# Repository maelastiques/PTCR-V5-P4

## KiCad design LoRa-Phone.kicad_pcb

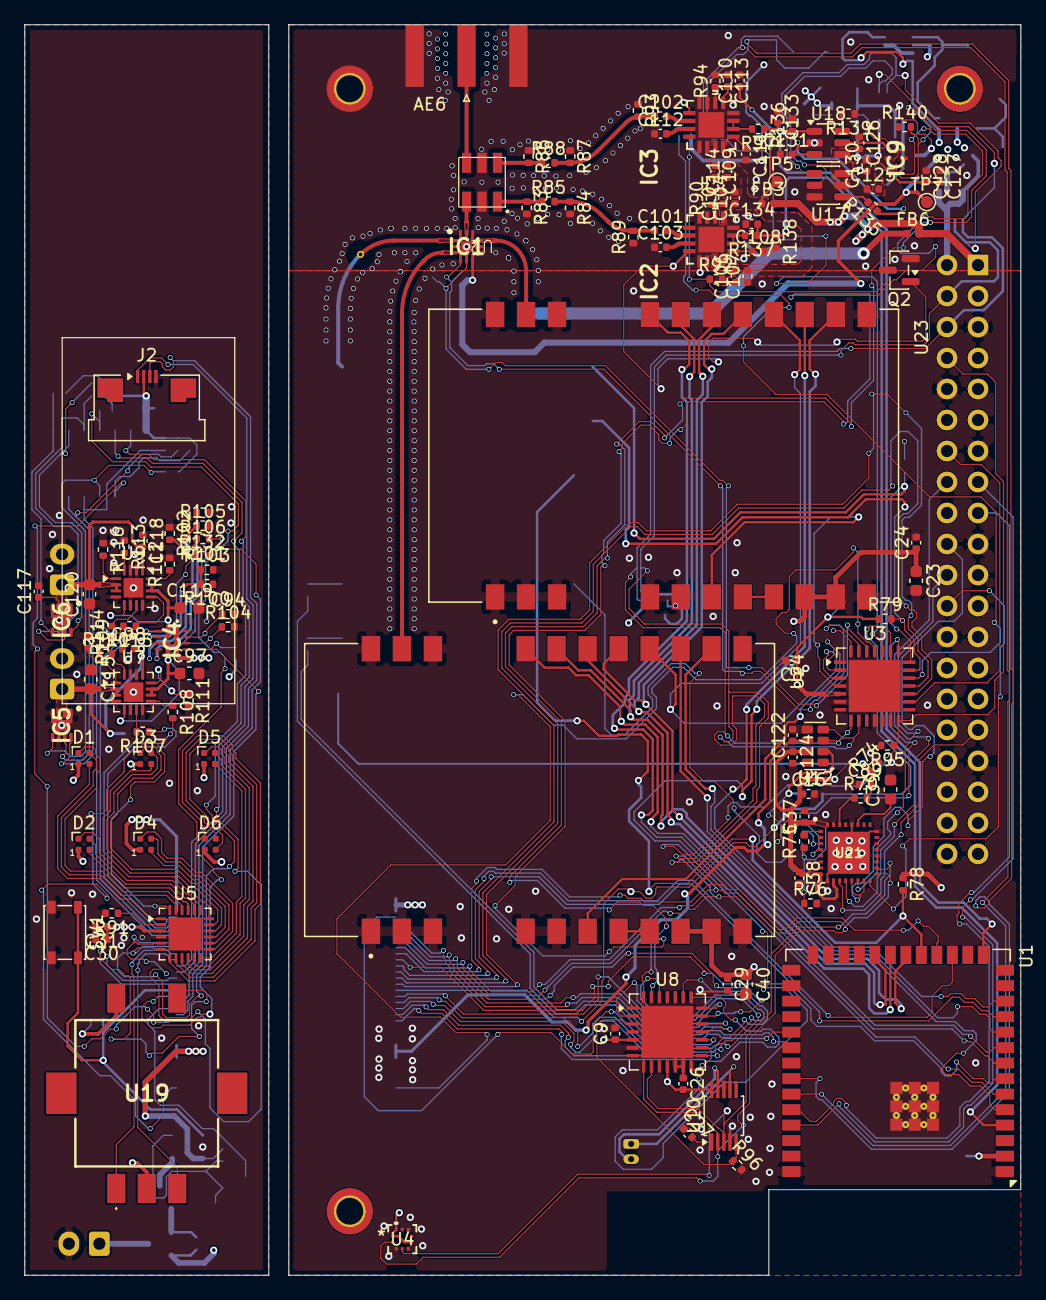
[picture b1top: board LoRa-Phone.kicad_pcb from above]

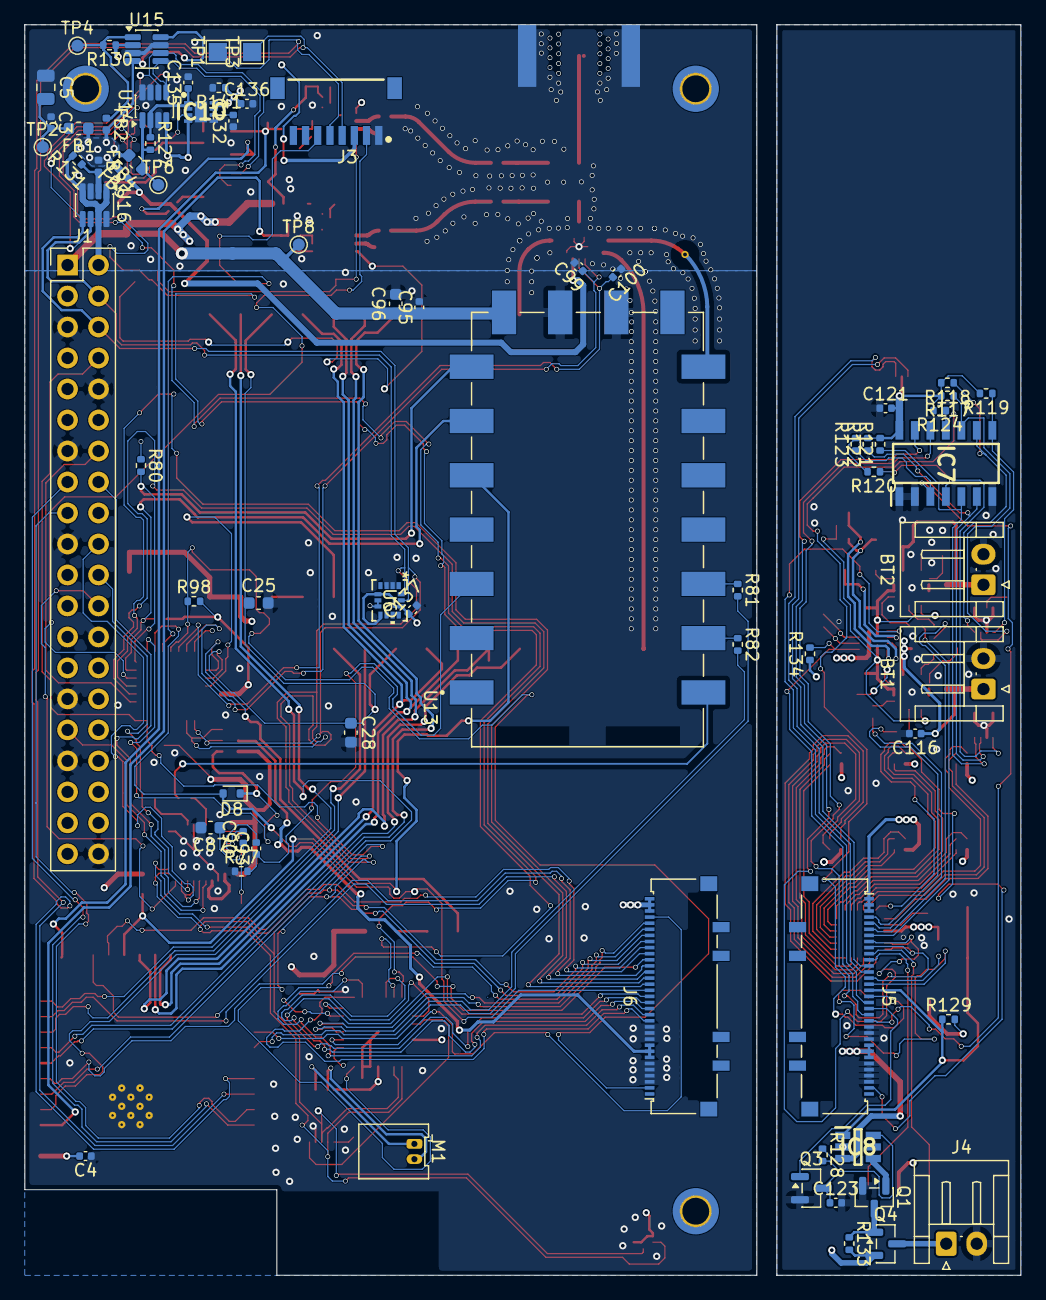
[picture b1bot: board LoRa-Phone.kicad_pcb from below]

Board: 4 copper layers, 81.6 x 102.5 mm, 203 parts (71 on the bottom side), 188 nets.

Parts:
AE6: SMA; SMA_Amphenol_132289_EdgeMount
BT1: MAIN; JST_EH_S2B-EH_1x02_P2.50mm_Horizontal
BT2: SECOND; JST_EH_S2B-EH_1x02_P2.50mm_Horizontal
C3, C4, C8, C9, C24, C29, C89, C90, C95, C121, C122, C123, C124, C125, C128, C130, C131, C132, C133, C134, C135, C137: 100nF; C_0402_1005Metric
C5: 47uF; C_0805_2012Metric
C16, C31, C37, C38, C94, C105, C107, C110, C114: 0.1uF; C_0402_1005Metric
C23, C25, C28, C40, C96: 10uF; C_0603_1608Metric
C26, C27, C30, C93, C98, C116, C117, C118: 1uF; C_0402_1005Metric
C39, C87, C97, C115, C119, C120: 4.7uF; C_0603_1608Metric
C99, C100, C104, C106, C109, C113: 100pF; C_0402_1005Metric
C101, C102, C103, C108, C111, C112: 1nF; C_0402_1005Metric
C126, C127: 2.2uF; C_0402_1005Metric
C136: 22uF; C_0402_1005Metric
D1, D2, D3, D4, D5, D6: LED_ARBG; LED_SK6812_EC15_1.5x1.5mm
D8: D; D_SOD-523
FB1: 600R @100MHz 2A; L_0603_1608Metric
FB2, FB3, FB5, FB6: 600R @100MHz 500mA; L_0402_1005Metric
FB4: 600R @100MHz 1.5A; L_0603_1608Metric
FB7: 600R @100MHz 4A; L_0402_1005Metric
IC1: SKY13373-460LF; QFN50P200X200X60-13N-D
IC2, IC3: AD8318ACPZ-REEL7; QFN65P400X400X100-17N
IC4: TPS2121RUXT
IC5, IC6: MAX17048G+T10; SON50P200X200X80-9N-D
IC7: TCA9543ADR; SOIC127P600X175-14N
IC8: MAX16150AUT+T; SOT95P280X145-6N
IC9: SN74LVC1G74RSE2
IC10: TPS22965NTDSGRQ1; SON50P200X200X80-9N
J1: Interface; PinHeader_2x20_P2.54mm_Vertical
J2: Joystick; Amphenol_F32Q-1A7x1-11004_1x04-1MP_P0.5mm_Horizontal
J3: L76K; JST_SM08B-SRSS-TB_LF__SN_
J4: JST_MAIN; JST_EH_S2B-EH_1x02_P2.50mm_Horizontal
J5, J6: Board_1; Molex_502244-3330_1x33-1MP_P0.5mm_Horizontal
M1: Motor_DC; Molex_PicoBlade_53048-0210_1x02_P1.25mm_Horizontal
MH0, MH0#2, MH0#3: MountingHole_2.2mm_M2_DIN965_Pad_TopBottom
Q1, Q2, Q3: AO3400A; SOT-23
Q4: AO3401A; SOT-23
R70, R74, R76, R78, R79, R80, R92, R95, R96, R98, R109, R116, R117, R118, R119, R120, R121, R122, R123, R124, R129, R132, R139, R140: 10K; R_0402_1005Metric
R75: 2.2K; R_0402_1005Metric
R77, R133: 100K; R_0402_1005Metric
R81, R82: 100R; R_0402_1005Metric
R83, R84, R86, R87: 96.2R; R_0402_1005Metric
R85, R88: 71.5R; R_0402_1005Metric
R89, R93: 52.3R; R_0402_1005Metric
R90, R94: 499R; R_0402_1005Metric
R91, R141: 3.3K; R_0402_1005Metric
R97, R137: 5.6K 0.1%; R_0402_1005Metric
R100, R101: 16K; R_0402_1005Metric
R102, R103, R106, R134: 5K; R_0402_1005Metric
R104, R128: 51.1K; R_0402_1005Metric
R105: 10.2K; R_0402_1005Metric
R107, R108, R114, R115, R135: 1K; R_0402_1005Metric
R110, R113: 1.13K; R_0402_1005Metric
R111, R112: 1.18K; R_0402_1005Metric
R127: 0.02R; R_0402_1005Metric
R130: 0.05R; R_0402_1005Metric
R131: 0.01R; R_0402_1005Metric
R136, R138: 10K 0.1%; R_0402_1005Metric
SW1: POWER; SW_SPST_PTS810
TP1: TXD_LC76G; TestPoint_Pad_1.5x1.5mm
TP2: +3V3_NSY; TestPoint_Pad_D1.0mm
TP3: RXD_LC76G; TestPoint_Pad_1.5x1.5mm
TP4: +3V3_GNSS; TestPoint_Pad_D1.0mm
TP5, TP8: +5V_RF; TestPoint_Pad_D1.0mm
TP6, TP7: +3V3_RF; TestPoint_Pad_D1.0mm
U1: ESP32-S3-WROOM-2
U2: TCD-10-23BDX+
U3, U8: MCP23017x-x-ML; QFN-28-1EP_6x6mm_P0.65mm_EP4.25x4.25mm
U4: BMP390; 10LGA_2X2X0p75_BOS
U5: IS31FL3218-QF; QFN-24-1EP_4x4mm_P0.5mm_EP2.7x2.7mm
U6: LSM6DSOXTR; LGA-14L_STM
U7, U9: BQ24075RGT; VQFN-16-1EP_3x3mm_P0.5mm_EP1.6x1.6mm
U10: DRV2605LDGS; TSSOP-10_3x3mm_P0.5mm
U12: RV-3028-C7; MicroCrystal_C7_SON-8_1.5x3.2mm_P0.9mm
U13: SA818S; XCVR_SA818S
U14, U15, U16: INA219BxDCN; SOT-23-8
U17: MCP4725xxx-xCH; SOT-23-6
U18: TLV3501AIDBV; SOT-23-6
U19: RIC11-31S10K2-GSMT; RIC1131S10K2GSMT
U21: WM8960; QFN-32
U23: E22-900M30S; XCVR_E22-900M30S
U24: E22-170M30S; XCVR_E22-900M30S

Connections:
+3V3: C4.2, C8.1, C9.1, C16.1, C26.2, C30.1, C31.1, C37.1, C38.1, C121.2, C124.1, C125.2, C126.2, C127.2, C128.2, C130.2, C137.1, D1.1 (A), D2.1 (A), D3.1 (A), D4.1 (A), D5.1 (A), D6.1 (A), FB1.1, FB2.2, FB4.2, FB5.2, FB7.1, IC7.14 (VCC), IC9.1 (~PRE), IC9.6 (D), IC9.8 (VCC), IC10.4 (VBIAS), J2.2, J5.1, J5.2, J5.3, J6.31, J6.32, J6.33, R78.1, R79.1, R80.1, R95.2, R98.2, R117.2, R118.2, R119.2, R120.2, R121.2, R122.2, R123.2, R124.2, R129.2, R134.1, R140.1, U1.2 (3V3), U3.5 (V_{DD}), U4.1 (VDDIO), U4.6 (CSB), U4.10 (VDD), U5.3 (VCC), U6.5 (VDDIO), U6.8 (VDD), U6.12 (CS), U8.5 (V_{DD}), U8.11 (A0), U10.10 (VDD), U12.7 (VDD), U14.4 (VS), U15.4 (VS), U15.8 (A1), U17.3 (VDD), U18.4 (V+), U19.C1 (NO), U19.D1 (S1), U21.8 (DCVDD), U21.10 (DBVDD), U21.32 (AVDD)
+3V3_GNSS: J3.3, R130.1, U15.2 (IN-)
+3V3_GNSS_IN: FB2.1, R130.2, TP4.1 (1_1), U15.1 (IN+)
+3V3_NSY: C3.2, C5.2, FB1.2, TP2.1 (1_1)
+3V3_RADIO: C23.1, C24.1, C29.1, C40.1, C136.1, IC10.7 (VOUT_1), IC10.8 (VOUT_2), R141.1, U23.9 (VIN), U23.10 (VIN), U24.9 (VIN), U24.10 (VIN)
+3V3_RADIO_IN: FB4.1, R127.2, TP6.1 (1_1), U14.1 (IN+)
+3V3_RADIO_OUT: C135.1, IC10.1 (VIN_1), IC10.2 (VIN_2), R127.1, U14.2 (IN-)
+3V3_RAW: J1.2 (3V3), J1.18 (3V3), R131.2, U16.1 (IN+), U16.4 (VS), U16.7 (A0)
+3V3_RF: FB5.1, IC1.6 (VDD), TP7.1 (1_1)
+5V: FB3.2, FB6.2, J1.1 (5V), J1.3 (5V)
+5V_RADIO: C95.1, C96.1, FB6.1, TP8.1 (1_1), U13.8 (VBAT)
+5V_RF: C104.1, C105.1, C106.2, C107.2, C109.1, C110.1, C113.2, C114.2, FB3.1, IC2.3 (VPSI_2), IC2.4 (VPSI), IC2.9 (VPSO), IC3.3 (VPSI_2), IC3.4 (VPSI), IC3.9 (VPSO), R92.2, TP5.1 (1_1)
AD8318_EN: IC2.16 (ENBL), Q2.1 (G), U3.28 (GPB3)
ANT: AE6.1 (A), U2.4 (OUTPUT)
BAT1: BT1.1 (+), C98.2, C115.2, C116.1, IC5.2 (CELL), IC5.3 (VDD), U7.2 (BAT), U7.3 (BAT), U7.13 (IN)
BAT1_CHG: J5.5, R108.2
BAT1_CHG_1: J6.29, U8.18 (GPA1)
BAT1_INT: IC5.5 (~ALRT), IC7.4 (~INT0), R120.1
BAT1_OUT: C97.1, IC4.7 (IN1), R101.1, R105.2, U7.5 (EN2), U7.10 (OUT), U7.11 (OUT)
BAT1_PGOOD: J5.4, R107.1
BAT1_PGOOD_1: J6.30, U8.17 (GPA0)
BAT2: BT2.1 (+), C117.1, C118.2, C120.2, IC6.2 (CELL), IC6.3 (VDD), U9.2 (BAT), U9.3 (BAT), U9.13 (IN)
BAT2_CHG: J5.7, R115.2
BAT2_CHG_1: J6.27, U8.20 (GPA3)
BAT2_INT: IC6.5 (~ALRT), IC7.8 (~INT1), R119.1
BAT2_OUT: C119.1, IC4.2 (IN2), R100.1, U9.5 (EN2), U9.10 (OUT), U9.11 (OUT)
BAT2_PGOOD: J5.6, R114.1
BAT2_PGOOD_1: J6.28, U8.19 (GPA2)
BATS_INT: IC7.11 (~INT), J5.17, R124.1
BATS_INT_1: J6.17, U8.21 (GPA4)
BATS_RESET: IC7.3 (~RESET), J5.21, R123.1
BATS_RESET_1: J6.13, U8.22 (GPA5)
BAT_OUT: C122.1, IC4.1 (OUT_1), IC4.8 (OUT_2), IC8.3 (VCC), J5.25, J5.26, J5.27, J6.7, J6.8, J6.9, Q4.2 (S), R128.1, R133.2, U12.6 (VBACKUP)
BAT_SEL: IC4.3 (CP2), J5.18, R132.1
BAT_SEL_1: J6.16, U8.2 (GPB5)
BAT_VAL: IC4.9 (ST), J5.20, R134.2
BAT_VAL_1: J6.14, U8.23 (GPA6)
BUSY_170: U1.5 (IO5), U24.14 (BUSY)
BUSY_900: U1.12 (IO8), U23.14 (BUSY)
BUTTON0: J6.19, U3.17 (GPA0)
BUTTON0_B: J5.15, U19.E1 (S2)
BUTTON1: J6.20, U3.18 (GPA1)
CLK: U1.20 (IO12), U23.18 (SCK), U24.18 (SCK)
CLK_SWITCH: IC9.7 (CLK), U18.5
CS_170: U1.9 (IO16), U24.19 (NSS)
CS_900: U1.8 (IO15), U23.19 (NSS)
D1B: D1.3 (BK), U5.23 (OUT17)
D1G: D1.4 (GK), U5.22 (OUT16)
D1R: D1.2 (RK), U5.1 (OUT18)
D2B: D2.3 (BK), U5.20 (OUT14)
D2G: D2.4 (GK), U5.19 (OUT13)
D2R: D2.2 (RK), U5.21 (OUT15)
D3B: D3.3 (BK), U5.17 (OUT11)
D3G: D3.4 (GK), U5.16 (OUT10)
D3R: D3.2 (RK), U5.18 (OUT12)
D4B: D4.3 (BK), U5.14 (OUT8)
D4G: D4.4 (GK), U5.13 (OUT7)
D4R: D4.2 (RK), U5.15 (OUT9)
D5B: D5.3 (BK), U5.11 (OUT5)
D5G: D5.4 (GK), U5.10 (OUT4)
D5R: D5.2 (RK), U5.12 (OUT6)
D6B: D6.3 (BK), U5.8 (OUT2)
D6G: D6.4 (GK), U5.7 (OUT1)
D6R: D6.2 (RK), U5.9 (OUT3)
DIO1_170: U1.10 (IO17), U24.13 (DIO1)
DIO1_900: U1.6 (IO6), U23.13 (DIO1)
FWD: C134.2, R137.1, R138.1, U1.4 (IO4)
FWD_IN: R83.1, R85.1, U2.1 (FWD)
FWD_OUT: C101.1, R84.1, R85.2, R89.2
GND: AE6.2 (Shield), BT1.2 (-), BT2.2 (-), C3.1, C4.1, C5.1, C8.2, C9.2, C16.2, C23.2, C24.2, C25.2, C26.1, C27.1, C28.2, C29.2, C30.2, C31.2, C37.2, C38.2, C39.2, C40.2, C87.2, C89.1, C94.2, C95.2, C96.2, C97.2, C98.1, C99.2, C100.1, C103.1, C104.2, C105.2, C106.1, C107.1, C108.2, C109.2, C110.2, C111.2, C112.1, C113.1, C114.1, C115.1, C116.2, C117.2, C118.1, C119.2, C120.1, C121.1, C122.2, C123.2, C124.2, C125.1, C126.1, C127.1, C128.1, C130.1, C131.1, C132.1, C133.1, C134.1, C135.2, C136.2, C137.2, IC1.2 (GND_1), IC1.7 (GND_2), IC1.8 (GND_3), IC1.10 (GND_4), IC1.12 (GND_5), IC1.13 (EPAD), IC2.1 (CMIP_2), IC2.2 (CMIP_3), IC2.8 (CMOP), IC2.11 (CMIP_4), IC2.12 (CMIP), IC2.17 (EP), IC3.1 (CMIP_2), IC3.2 (CMIP_3), IC3.8 (CMOP), IC3.11 (CMIP_4), IC3.12 (CMIP), IC3.17 (EP), IC4.12 (GND), IC5.1 (CTG), IC5.4 (GND), IC5.6 (QSTRT), IC5.9 (EP), IC6.1 (CTG), IC6.4 (GND), IC6.6 (QSTRT), IC6.9 (EP), IC7.1 (A0), IC7.2 (A1), IC7.7 (GND), IC8.2 (GND), IC9.4 (GND), IC10.5 (GND), IC10.9 (EP), J1.5 (GND), J1.10 (GND), J1.13 (GND), J1.19 (GND), J1.26 (GND), J1.29 (GND), J1.33 (GND), J1.40 (GND), J2.4, J3.1, J4.2, J5.22, J5.23, J5.24, J5.28, J5.29, J5.30, J5.31, J6.3, J6.4, J6.5, J6.6, J6.10, J6.11, J6.12, MH0#2.1, Q1.2 (S), Q2.2 (S), Q3.2 (S), R74.2, R76.2, R77.1, R83.2, R84.2, R86.1, R87.1, R89.1, R90.2, R91.2, R93.1, R94.2, R96.2, R102.1, R103.2, R104.2, R106.1, R109.1, R110.1, R111.2, R112.2, R113.1, R116.1, R132.2, R136.2, R138.2, R139.1, R141.2, SW1.2, U1.1 (GND), U1.40 (GND), U1.41 (GND), U2.2 (GND), U2.5 (NC), U3.6 (V_{SS}), U3.11 (A0), U3.12 (A1), U3.13 (A2), U3.29 (EP), U4.3 (VSS), U4.5 (SDO), U4.8 (VSS), U4.9 (VSS), U5.4 (GND), U5.25 (GND), U6.1 (SDO/SA0), U6.2 (SDX), U6.3 (SCX), U6.6 (GND), U6.7 (GND), U7.4 (~CE), U7.6 (EN1), U7.8 (VSS), U7.14 (TMR), U7.15 (SYSOFF), U7.17 (VSS), U8.6 (V_{SS}), U8.12 (A1), U8.13 (A2), U8.29 (EP), U9.4 (~CE), U9.6 (EN1), U9.8 (VSS), U9.14 (TMR), U9.15 (SYSOFF), U9.17 (VSS), U10.4 (IN/TRIG), U10.8 (GND), U12.5 (VSS), U13.9 (GND), U13.10 (GND), U14.3 (GND), U14.7 (A0), U14.8 (A1), U15.3 (GND), U15.7 (A0), U16.3 (GND), U16.8 (A1), U17.2 (VSS), U17.6 (A0), U18.2 (V-), U21.9 (DGND), U21.20 (SPKGND2), U21.24 (SPKGND1), U21.28 (AGND), U21.PADDLE (GNDPADDLE), U23.1 (GND), U23.2 (GND), U23.3 (GND), U23.4 (GND), U23.5 (GND), U23.11 (GND), U23.12 (GND), U23.20 (GND), U23.22 (GND), U24.1 (GND), U24.2 (GND), U24.3 (GND), U24.4 (GND), U24.5 (GND), U24.11 (GND), U24.12 (GND), U24.20 (GND), U24.22 (GND)
GNSS_CTRL: J3.2, U3.19 (GPA2)
GNSS_RX: J3.5, TP1.1 (1_1), U1.34 (MTDI/IO41)
GNSS_TX: J3.4, TP3.1 (1_1), U1.35 (MTMS/IO42)
GNSS_WAKE: J3.6, U3.24 (GPA7)
G_RESET: J3.8, U8.25 (GPB0)
H/L: R80.2, U3.21 (GPA4), U13.7 (H/L)
INTA_MCP_1: J1.14 (GPIO4), U3.16 (INTA)
INTA_MCP_2: J1.11 (GPIO5), U8.16 (INTA)
INT_RTC: D8.1 (K), U3.22 (GPA5), U12.2 (~INT)
JOYSTICK_X: J6.22, U1.17 (IO9)
JOYSTICK_X_B: J2.1, J5.12
JOYSTICK_Y: J6.21, U1.11 (IO18)
JOYSTICK_Y_B: J2.3, J5.13
LINPUT1: C93.1, R77.2, U13.3 (AF_OUT)
MIC_HS: C87.1, C90.1, R75.1, R76.1
MISO: U1.22 (IO14), U23.16 (MISO), U24.16 (MISO)
MONO_OUT: C89.2, R70.2, R74.1, U13.18 (MIC_IN)
MOSI: U1.21 (IO13), U23.17 (MOSI), U24.17 (MOSI)
MOTOR: R96.1, U8.3 (GPB6), U10.5 (EN)
NRST_RADIO: C25.1, C28.1, U3.3 (GPB6), U23.15 (~RST), U24.15 (~RST)
unnamed: C108.1, IC2.5 (CLPF)
unnamed: C101.2, IC2.14 (INHI)
unnamed: C103.2, IC2.15 (INLO)
unnamed: IC2.10 (TADJ), R90.1
unnamed: IC2.6 (VOUT), IC2.7 (VSET), R137.2
unnamed: C111.1, IC3.5 (CLPF)
unnamed: IC3.16 (ENBL), Q2.3 (D), R92.1
unnamed: C102.2, IC3.14 (INHI)
unnamed: C112.2, IC3.15 (INLO)
unnamed: IC3.10 (TADJ), R94.1
unnamed: IC3.6 (VOUT), IC3.7 (VSET), R97.2
unnamed: IC4.10 (ILIM), R104.1
unnamed: IC4.5 (OV1), R101.2, R102.2
unnamed: IC4.4 (OV2), R100.2, R103.1
unnamed: IC4.6 (PR1), R105.1, R106.2
unnamed: C94.1, IC4.11 (SS)
unnamed: IC8.4 (OUT), Q1.1 (G)
unnamed: C123.1, IC8.6 (~CLR), Q3.3 (D), R128.2
unnamed: C132.2, IC10.6 (CT)
unnamed: J4.1, Q4.3 (D)
unnamed: M1.1 (+), U10.7 (OUT+)
unnamed: M1.2 (-), U10.9 (OUT-)
unnamed: Q1.3 (D), Q4.1 (G), R133.1
unnamed: R81.2, U1.31 (IO38)
unnamed: R82.2, U1.32 (MTCK/IO39)
unnamed: R91.1, U5.2 (R_EXT)
unnamed: R111.1, U7.12 (ILIM)
unnamed: R110.2, U7.16 (ISET)
unnamed: R109.2, U7.1 (TS)
unnamed: R108.1, U7.9 (~CHG)
unnamed: R107.2, U7.7 (~PGOOD)
unnamed: R112.1, U9.12 (ILIM)
unnamed: R113.2, U9.16 (ISET)
unnamed: R116.2, U9.1 (TS)
unnamed: R115.1, U9.9 (~CHG)
unnamed: R114.2, U9.7 (~PGOOD)
unnamed: C27.2, U10.1 (REG)
unnamed: FB7.2, R131.1, U16.2 (IN-)
unnamed: R135.2, U17.1 (VOUT)
unnamed: C93.2, U21.4 (LINPUT1)
unnamed: C90.2, U21.3 (LINPUT2)
unnamed: R75.2, U21.1 (MICBIAS)
unnamed: R70.1, U21.30 (MONO_OUT)
unnamed: C39.1, U21.27 (VMID)
unnamed: U23.7 (TXEN), U23.8 (DIO2)
unnamed: U24.7 (TXEN), U24.8 (DIO2)
PD: R79.2, U3.20 (GPA3), U13.6 (PD)
POWER_BTN: D8.2 (A), IC8.1 (~PB_IN), J5.16, J6.18, R129.1, SW1.1, U3.23 (GPA6)
PTT: R78.2, U1.19 (IO11), U13.5 (PTT)
RESET_MCP: J1.8 (GPIO2), R95.1, U3.14 (~RESET), U8.14 (~RESET)
REV: C133.2, R97.1, R136.1, U1.15 (IO3), U18.1 (-)
REV_IN: R86.2, R88.1, U2.6 (REV)
REV_OUT: C102.1, R87.2, R88.2, R93.2
RF1: IC1.1 (J1), U13.12 (ANT)
RF2: IC1.9 (J2), U23.21 (ANT)
RF3: IC1.3 (J3), U24.21 (ANT)
RFS_V1: C99.1, IC1.4 (V1), U3.27 (GPB2)
RFS_V2: C100.2, IC1.5 (V2), U3.26 (GPB1)
RF_FAULT: IC9.3 (Q), U8.27 (GPB2)
RF_FAULT_RESET: IC9.2 (~CLR), R140.2, U8.28 (GPB3)
ROS: IC1.11 (RFC), U2.3 (INPUT)
ROT_ENC1: J6.24, U1.18 (IO10)
ROT_ENC1_B: J5.10, U19.A1 (COM1)
ROT_ENC2: J6.23, U1.7 (IO7)
ROT_ENC2_B: J5.11, U19.B1 (COM2)
RXEN_170: U3.2 (GPB5), U24.6 (RXEN)
RXEN_900: U3.4 (GPB7), U23.6 (RXEN)
S3_BOOT: J1.38 (GPIO52), U1.27 (IO0)
S3_EN: J1.36 (GPIO51), U1.3 (EN)
S3_IRQ: J1.34 (GPIO50), U1.38 (IO2)
S3_RXD0: J1.15 (GPIO21), U1.37 (TXD0/IO43)
S3_TXD0: J1.17 (GPIO22), U1.36 (RXD0/IO44)
SA818S_RXD: R81.1, U13.16 (RXD)
SA818S_TXD: R82.1, U13.17 (TXD)
SC0: IC5.7 (SCL), IC7.6 (SC0), R122.1
SC1: IC6.7 (SCL), IC7.10 (SC1), R117.1
SCL: J1.6 (GPIO8), J6.25, U3.8 (SCK), U4.2 (SCK), U6.13 (SCL), U8.8 (SCK), U10.2 (SCL), U12.3 (SCL), U14.5 (SCL), U15.5 (SCL), U16.5 (SCL), U17.5 (SCL), U21.17 (SCL)
SCL_B: IC7.12 (SCL), J5.9, U5.6 (SCL)
SD0: IC5.8 (SDA), IC7.5 (SD0), R121.1
SD1: IC6.8 (SDA), IC7.9 (SD1), R118.1
SDA: J1.4 (GPIO7), J6.26, U3.9 (SDA), U4.4 (SDI), U6.14 (SDA), U8.9 (SDA), U10.3 (SDA), U12.4 (SDA), U14.6 (SDA), U15.6 (SDA), U16.6 (SDA), U17.4 (SDA), U21.18 (SDA)
SDA_B: IC7.13 (SDA), J5.8, U5.5 (SDA)
SDB: J5.32, U5.24 (~SDB)
SDB_1: J6.2, R98.1, U3.25 (GPB0)
SHDN_COMP: R139.2, U8.1 (GPB4), U18.6 (SHDN)
SHUTDOWN: J5.19, Q3.1 (G)
SHUTDOWN_1: J6.15, U8.26 (GPB1)
SPI_CLK: J1.35 (GPIO46), U1.24 (IO47)
SPI_CS: J1.32 (GPIO49), U1.39 (IO1)
SPI_MISO: J1.39 (GPIO48), U1.23 (IO21)
SPI_MOSI: J1.37 (GPIO47), U1.25 (IO48)
TPS22965_ON: IC9.5 (~Q), IC10.3 (ON)
VOUT_ADC: C131.2, R135.1, U18.3 (+)
WM8960_ACDDAT: J1.24 (GPIO31), U21.16 (ADCDAT)
WM8960_BLCK: J1.16 (GPIO28), U21.12 (BCLK)
WM8960_DACDAT: J1.22 (GPIO30), U21.14 (DACDAT)
WM8960_DAC/ADC_LRC: J1.20 (GPIO29), U21.13 (DACLRC), U21.15 (ADCLRC/GPIO)
WM8960_MLCK: J1.31 (GPIO32), U21.11 (MCLK)

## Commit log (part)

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2026-06-16 Added the first test electrical schematic for PTCR V5 P4
2026-06-17 Routed RF Core
2026-06-18 Routed RF part and started routing MCU, SPI Bus, and other
2026-06-19 Modified schematic to add dual battery with dual charger, dual gauge and power mux
2026-06-19 Added power button latch logic, consumption logic, RTC
2026-06-26 Routed secondary PCB with Power and charging managment, and routed FPC Connector
